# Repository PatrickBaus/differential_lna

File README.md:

Low Noise Differential Amplifier
===================

This repository contains the schematics and mechanical files for a low noise diffrential amplifier based on the Linear Technologies [AN-159](https://www.analog.com/media/en/technical-documentation/app-notes/an-159.pdf).

Key Features:
 * Bandwidth (-3 dB): 10 Hz - 1.5 MHz
 * Gain: 80 dB (10.000)
 * Noise floor 500 pV/Hz^-1/2
 * Note: Requires a very low source impedance! Less than 10 Ohm.

The design was done using [KiCAD 7](https://www.kicad.org/).

Mechanical Design
------------------------------
The PCB should be housed in a mild steel box (e.g. cookie jar).

About
-----

The root folder contains the KiCAD files, while the gerber files can be found in the [/gerber](gerber/) folder, the bill of materials in the [/bom](bom/) folder.

Related Repositories
--------------------

See the following repositories for more information

KiCAD footprints: https://github.com/PatrickBaus/footprints.pretty

KiCAD 3D models: https://github.com/PatrickBaus/footprints.3dshapes

KiCAD schematic libraries: https://github.com/PatrickBaus/KiCad-libraries

License
-------

This work is released under the Cern OHL v.1.2
See www.ohwr.org/licenses/cern-ohl/v1.2 or the included LICENSE file for more information.

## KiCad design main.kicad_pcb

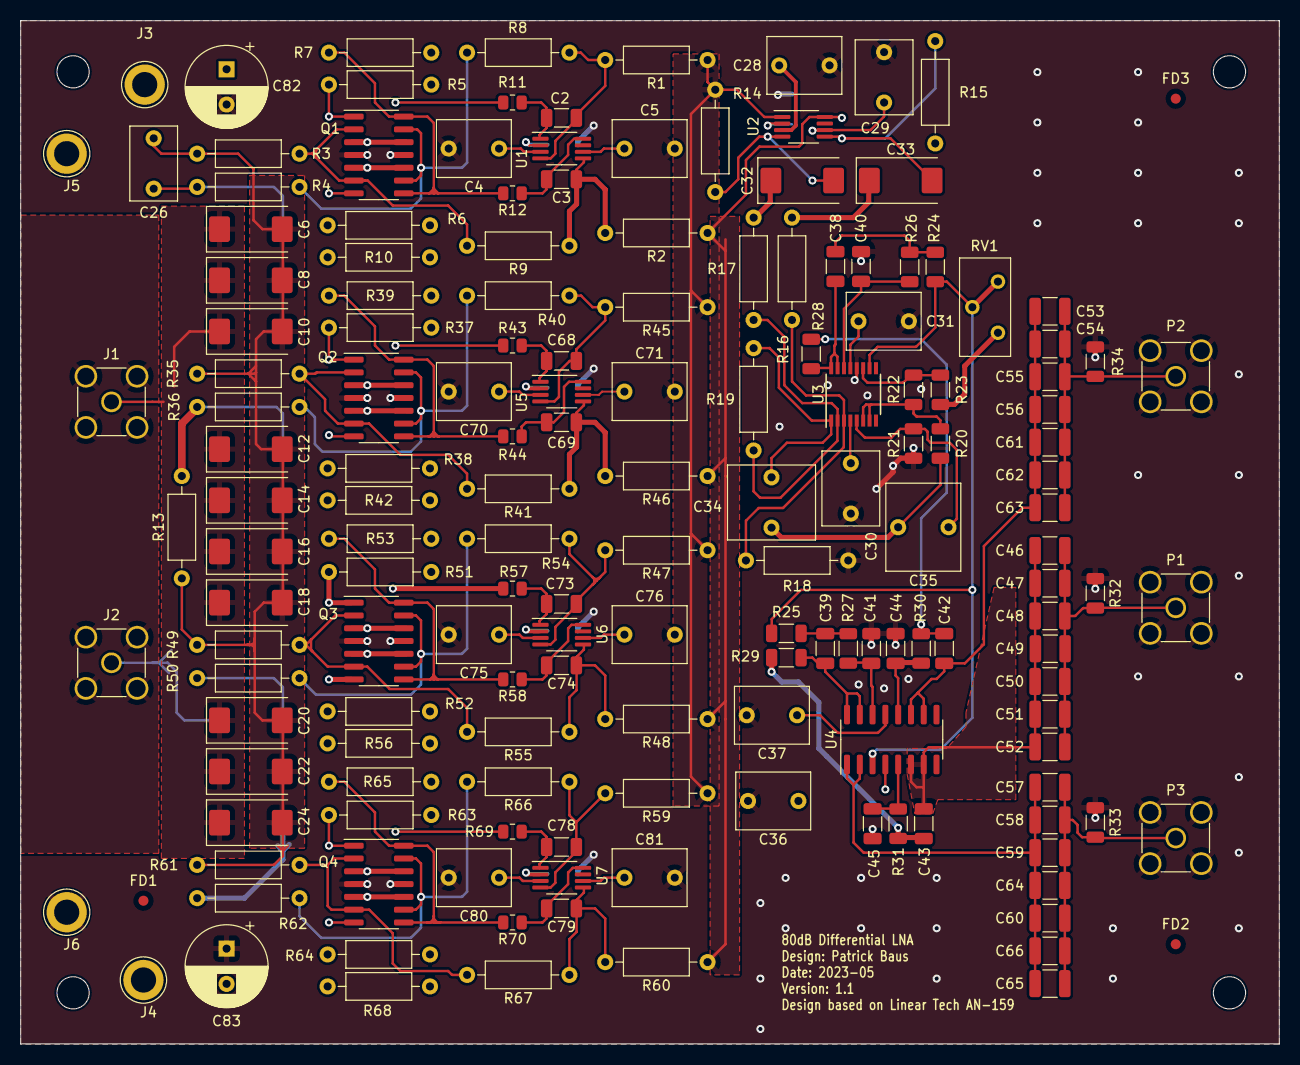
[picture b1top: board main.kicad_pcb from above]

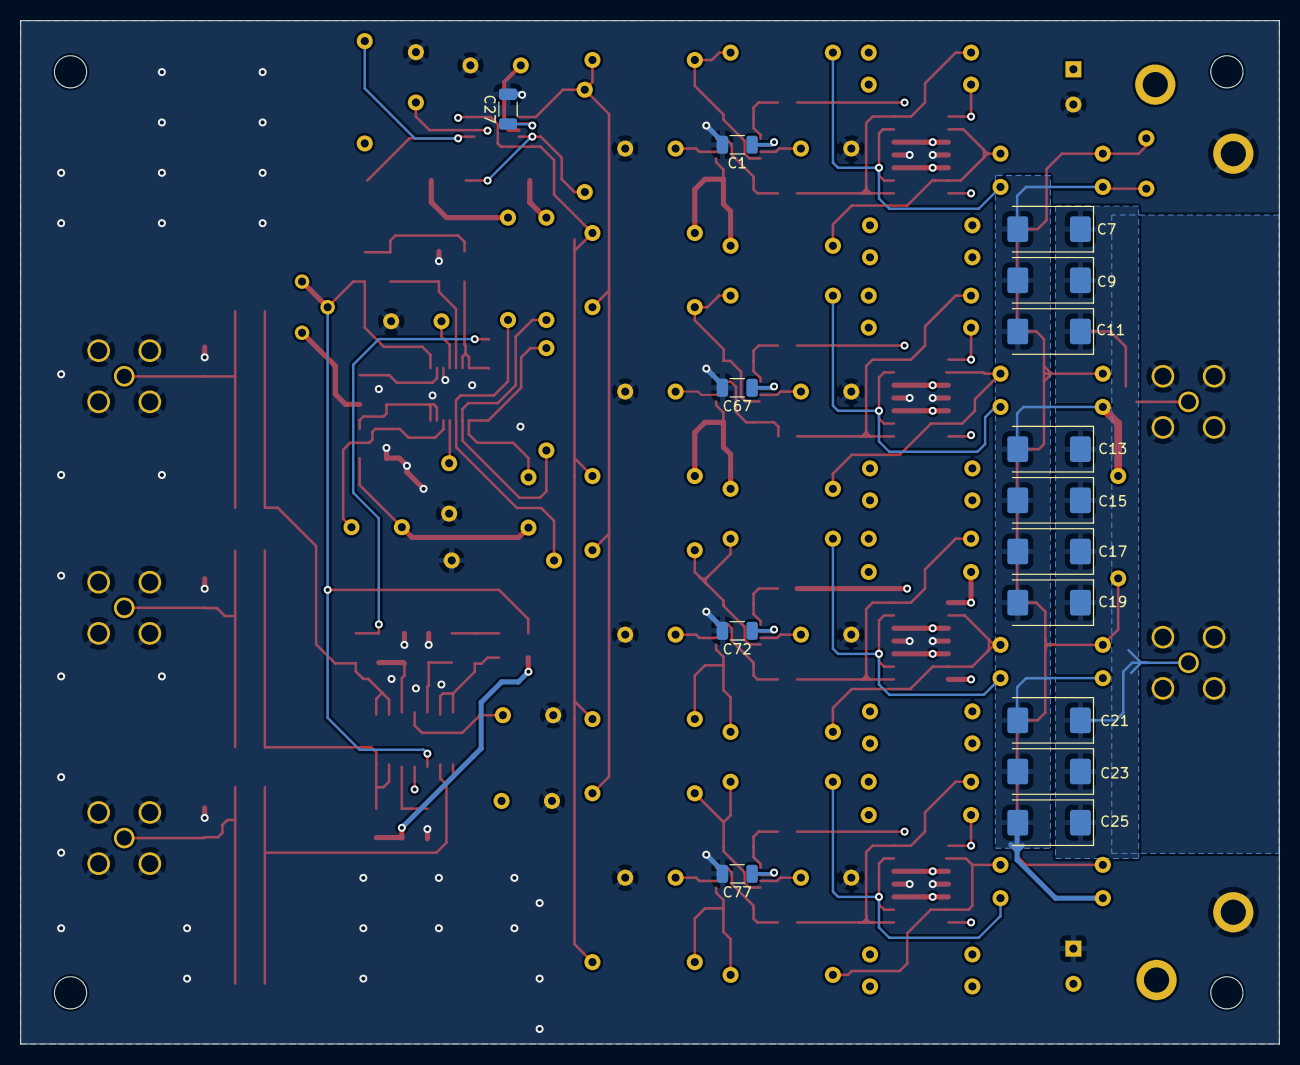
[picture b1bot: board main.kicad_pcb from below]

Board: 4 copper layers, 125.0 x 101.6 mm, 181 parts (15 on the bottom side), 84 nets.

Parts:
C1, C27, C67, C72, C77: 1u; C_1206_3216Metric
C2, C3, C68, C69, C73, C74, C78, C79: 33p; C_1206_3216Metric
C4, C5, C28, C29, C30, C31, C36, C37, C70, C71, C75, C76, C80, C81: 1u; C_Rect_L7.2mm_W5.5mm_P5.00mm_FKS2_FKP2_MKS2_MKP2
C6, C7, C8, C9, C10, C11, C12, C13, C14, C15, C16, C17, C18, C19, C20, C21, C22, C23, C24, C25: 150u; CP_EIA-7343-43_Kemet-X
C26: 2.2n; C_Rect_L7.2mm_W4.5mm_P5.00mm_FKS2_FKP2_MKS2_MKP2
C32, C33: 330u; CP_EIA-7343-31_Kemet-D
C34, C35: 4.7u; C_Rect_L7.2mm_W8.5mm_P5.00mm_FKP2_FKP2_MKS2_MKP2
C38: 120p; C_1206_3216Metric
C39: 1.2n; C_1206_3216Metric
C40: 100p; C_1206_3216Metric
C41: 1n; C_1206_3216Metric
C42: 150p; C_1206_3216Metric
C43: 1.5n; C_1206_3216Metric
C44: 22p; C_1206_3216Metric
C45: 220p; C_1206_3216Metric
C46, C47, C48, C49, C50, C51, C52, C53, C54, C55, C56, C57, C58, C59, C60, C61, C62, C63, C64, C65, C66: 100u; C_1210_3225Metric
C82, C83: 180u; CP_Radial_D8.0mm_P3.50mm
FD1, FD2, FD3: FIDUCIAL; Fiducial_1mm_Mask2mm
H1, H2, H3, H4: MountingHole; MountingHole_3.2mm_M3_DIN965
J1, J2: SMA; SMA_Amphenol_901-144_Vertical
J3, J4, J5, J6: CONN_01X01; TestPoint_Loop_D3.80mm_Drill2.5mm
P1, P2, P3: SMA; SMA_Amphenol_901-144_Vertical
Q1, Q2, Q3, Q4: THAT300; SOIC-14_3.9x8.7mm_P1.27mm
R1, R2, R45, R46, R47, R48, R59, R60: 100; R_Axial_DIN0207_L6.3mm_D2.5mm_P10.16mm_Horizontal
R3, R4, R35, R36, R49, R50, R61, R62: 49.9; R_Axial_DIN0207_L6.3mm_D2.5mm_P10.16mm_Horizontal
R5, R6, R7, R10, R37, R38, R39, R42, R51, R52, R53, R56, R63, R64, R65, R68: 4.02k; R_Axial_DIN0207_L6.3mm_D2.5mm_P10.16mm_Horizontal
R8, R9, R40, R41, R54, R55, R66, R67: 1.3k; R_Axial_DIN0207_L6.3mm_D2.5mm_P10.16mm_Horizontal
R11, R12, R43, R44, R57, R58, R69, R70: 1k; R_0805_2012Metric
R13, R18, R19: 1k; R_Axial_DIN0207_L6.3mm_D2.5mm_P10.16mm_Horizontal
R14, R15: 249; R_Axial_DIN0207_L6.3mm_D2.5mm_P10.16mm_Horizontal
R16, R17: 475; R_Axial_DIN0207_L6.3mm_D2.5mm_P10.16mm_Horizontal
R20: 2k; R_1206_3216Metric
R21: 5.76k; R_1206_3216Metric
R22: 100; R_1206_3216Metric
R23: 1.5k; R_1206_3216Metric
R24, R25: 1.69k; R_1206_3216Metric
R26, R27: 1.24k; R_1206_3216Metric
R28, R29: 4.02k; R_1206_3216Metric
R30, R31: 2.15k; R_1206_3216Metric
R32, R33, R34: 49.9; R_1206_3216Metric
RV1: 1k; Potentiometer_Bourns_3296Y_Vertical
U1, U2, U5, U6, U7: LT1994; MSOP-8_3x3mm_P0.65mm
U3: LT6232; SSOP-16_3.9x4.9mm_P0.635mm
U4: LT1365; SOIC-16_3.9x9.9mm_P1.27mm

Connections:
/2nd stage differential/IN+: R1.1, R14.2, R45.1, R47.1, R59.1, U2.1
/2nd stage differential/IN-: R2.1, R15.2, R46.1, R48.1, R60.1, U2.8
/2nd stage differential/OUT+: C33.2, R15.1, U2.5
/2nd stage differential/OUT-: C32.2, R14.1, U2.4
/2nd stage differential/V+: C4.1, C28.1, C30.1, C36.1, C70.1, C75.1, C80.1, C82.1, J3.1, R5.1, R7.1, R37.1, R39.1, R51.1, R53.1, R63.1, R65.1, U1.3, U2.3, U3.4 (V+), U4.4 (V+), U5.3, U6.3, U7.3
/2nd stage differential/V-: C5.1, C29.1, C31.1, C37.1, C71.1, C76.1, C81.1, C83.2, J4.1, R6.2, R10.2, R38.2, R42.2, R52.2, R56.2, R64.2, R68.2, U1.6, U2.6, U3.13 (V-), U4.13 (V-), U5.6, U6.6, U7.6
/Differential to single ended/OUT: R20.2, R22.2, U3.6 (-), U3.7
/Final amplifier stage/OUT: R24.2, R25.2, RV1.2, RV1.3, U3.10, U4.3 (+)
/Input Filter/In+: C6.1, C8.1, C10.1, C12.1, C14.1, C16.1, C18.1, C20.1, C22.1, C24.1, J1.1 (In)
/Input Filter/In-: C7.1, C9.1, C11.1, C13.1, C15.1, C17.1, C19.1, C21.1, C23.1, C25.1, J2.1 (In)
/Input Filter/Out+: C6.2, C8.2, C10.2, C12.2, C14.2, C16.2, C18.2, C20.2, C22.2, C24.2, C26.1, R3.2, R13.1, R35.2, R49.2, R61.2
/Input Filter/Out-: C7.2, C9.2, C11.2, C13.2, C15.2, C17.2, C19.2, C21.2, C23.2, C25.2, C26.2, R4.2, R13.2, R36.2, R50.2, R62.2
/Output/OUT: C57.1, C58.1, C59.1, C60.1, C64.1, C65.1, C66.1, P3.1 (In), R33.2
/Output/OUT_1MHz: C53.1, C54.1, C55.1, C56.1, C61.1, C62.1, C63.1, P2.1 (In), R34.2
/Output/OUT_100kHz: C46.1, C47.1, C48.1, C49.1, C50.1, C51.1, C52.1, P1.1 (In), R32.2
/Preamplifier 2/OUT+: C68.1, R40.1, R45.2, U5.4
/Preamplifier 2/OUT-: C69.1, R41.1, R46.2, U5.5
/Preamplifier 3/OUT+: C73.1, R47.2, R54.1, U6.4
/Preamplifier 3/OUT-: C74.1, R48.2, R55.1, U6.5
/Preamplifier 4/OUT+: C78.1, R59.2, R66.1, U7.4
/Preamplifier 4/OUT-: C79.1, R60.2, R67.1, U7.5
/Preamplifier/OUT+: C2.1, R1.2, R8.1, U1.4
/Preamplifier/OUT-: C3.1, R2.2, R9.1, U1.5
GND: C1.2, C4.2, C5.2, C27.2, C28.2, C29.2, C30.2, C31.2, C36.2, C37.2, C40.2, C41.2, C44.2, C45.2, C67.2, C70.2, C71.2, C72.2, C75.2, C76.2, C77.2, C80.2, C81.2, C82.2, C83.1, J5.1, J6.1, P1.2 (Ext), P2.2 (Ext), P3.2 (Ext), Q1.4 (B), Q1.11 (E), Q2.4 (B), Q2.11 (E), Q3.4 (B), Q3.11 (E), Q4.4 (B), Q4.11 (E), R18.2, R21.2, R32.1, R33.1, R34.1, U3.12 (+)
GNDPWR: J1.2 (Ext), J2.2 (Ext)
unnamed: C1.1, U1.2
unnamed: C2.2, R11.1, U1.1
unnamed: C3.2, R12.1, U1.8
unnamed: C27.1, U2.2
unnamed: C32.1, R17.2
unnamed: C33.1, R16.2
unnamed: C34.1, C35.2, R20.1
unnamed: C34.2, R19.2, U3.1
unnamed: C38.2, R24.1, R26.2
unnamed: C39.2, R25.1, R27.2
unnamed: C42.2, R28.1, R30.2
unnamed: C43.2, R29.1, R31.2
unnamed: C67.1, U5.2
unnamed: C68.2, R43.1, U5.1
unnamed: C69.2, R44.1, U5.8
unnamed: C72.1, U6.2
unnamed: C73.2, R57.1, U6.1
unnamed: C74.2, R58.1, U6.8
unnamed: C77.1, U7.2
unnamed: C78.2, R69.1, U7.1
unnamed: C79.2, R70.1, U7.8
unnamed: Q1.2 (B), Q1.6 (B), R3.1, R9.2
unnamed: Q1.1 (C), Q1.7 (C), R5.2, R11.2
unnamed: Q1.3 (E), Q1.12 (E), R6.1
unnamed: Q1.9 (B), Q1.13 (B), R4.1, R8.2
unnamed: Q1.8, Q1.14 (C), R7.2, R12.2
unnamed: Q1.5 (E), Q1.10 (E), R10.1
unnamed: Q2.2 (B), Q2.6 (B), R35.1, R41.2
unnamed: Q2.1 (C), Q2.7 (C), R37.2, R43.2
unnamed: Q2.3 (E), Q2.12 (E), R38.1
unnamed: Q2.9 (B), Q2.13 (B), R36.1, R40.2
unnamed: Q2.8, Q2.14 (C), R39.2, R44.2
unnamed: Q2.5 (E), Q2.10 (E), R42.1
unnamed: Q3.2 (B), Q3.6 (B), R49.1, R55.2
unnamed: Q3.1 (C), Q3.7 (C), R51.2, R57.2
unnamed: Q3.3 (E), Q3.12 (E), R52.1
unnamed: Q3.9 (B), Q3.13 (B), R50.1, R54.2
unnamed: Q3.8, Q3.14 (C), R53.2, R58.2
unnamed: Q3.5 (E), Q3.10 (E), R56.1
unnamed: Q4.2 (B), Q4.6 (B), R61.1, R67.2
unnamed: Q4.1 (C), Q4.7 (C), R63.2, R69.2
unnamed: Q4.3 (E), Q4.12 (E), R64.1
unnamed: Q4.9 (B), Q4.13 (B), R62.1, R66.2
unnamed: Q4.8, Q4.14 (C), R65.2, R70.2
unnamed: Q4.5 (E), Q4.10 (E), R68.1
unnamed: R23.1, RV1.1
unnamed: R16.1, R18.1, U3.3 (+)
unnamed: R17.1, R19.1, U3.2 (-)
unnamed: C35.1, R21.1, U3.5 (+)
unnamed: R22.1, R23.2, U3.11 (-)
unnamed: C40.1, R26.1, U3.14 (+)
unnamed: C38.1, R28.2, U3.15 (-), U3.16
unnamed: C57.2, C58.2, C59.2, C60.2, C64.2, C65.2, C66.2, U4.1, U4.2 (-)
unnamed: C45.1, R31.1, U4.5 (+)
unnamed: C43.1, C46.2, C47.2, C48.2, C49.2, C50.2, C51.2, C52.2, U4.6 (-), U4.7
unnamed: C44.1, R30.1, U4.12 (+)
unnamed: C42.1, C53.2, C54.2, C55.2, C56.2, C61.2, C62.2, C63.2, U4.10, U4.11 (-)
unnamed: C41.1, R27.1, U4.14 (+)
unnamed: C39.1, R29.2, U4.15 (-), U4.16

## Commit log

2023-05-02 Added readme
2023-05-02 Added license file
2023-05-02 Removed invalid image url
2023-05-02 Update README.md
    Updated noise figure with LaTeX
2023-05-03 Added silkscreen labels to input and outputs
